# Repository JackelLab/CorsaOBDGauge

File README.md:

Bluetooth OBD Based Gauge For The Vauxhall/Opel Corsa

Anyone who owns an early Corsa knows you can't show the battery percentage on the dash
without having the car plugged in to a charger. The only other way is using an app on
your phone connected to and Bluetooth OBD adaptor (or WiFi adaptor if you have an iphone).

The problem with using an app (like 'Car Scanner' is that you need to connect to the
adaptor and then the car every time you want to see the data.

I decided (too long ago) that I wanted to make a display which showed the battery
percentage so it was always visible. My biggest stumbling block to this was understanding
what requests to send to the car and how to decode this data. After sometime, I found
some details on another github page 'EVNotify' which mentioned what data needed to be
sent and what the responses would be:
https://github.com/EVNotify/EVNotify/issues/205

With this information, I was finally able to get access to the data from the car.

I built a PCB with an ESP32-WROVER-IE as the main processor as it has Bluetooth built in,
a 0.96" LCD from ebay with 160 x 80 pixel 65k colours.

The features I've added so far are:

SOC        - Battery state of charge. I've used the non calibrated version, I don't know
what the differences are.

SOH        - Battery state of health. This only shows after the unit has setup and
checked communications with the OBD adaptor and car.

SOC Delta  - State of charge change. This shows to SOC change since the unit was powered
up, ideal for tracking how much battery has been used for a journey or how much battery
has been added while charging.

Temperature - Battery temperature.

Speed       - Shows the speed in 100th of MPH which can be re-calibrated if measured
against a GPS speedo.

Voltage     - OBD 12V battery voltage. Measured at the OBD adaptor.

Est. Range  - Estimated range based on speed and battery percentage used over the last
minute and 5 minutes.

There is a reed switch to change the display modes, the gauge will remember the last mode
and restore it at power up.

The ELM327 OBD.

When selecting a Bluetooth OBD adaptor, you will need to find one with the PIC18F25K80
chip. May of the adaptors for sale will say they are PIC versions, but often, they are
emulated versions and for whatever reason, the ESP32 can't communicate correctly with
them and just receives echoed data back.

So, ELM Electronics created the ELM327 chip for communicating with the OBD port on
vehicles, but with their version 1.5 software, chips where sent out without the code
protection on and so this code has been copied by may of the Chinese manufactures making
the currently available adaptors. If the adaptor you are looking to buy has any mention of
V2.1, then it is more likely a chip pretending to be a PIC.

The only way to really confirm that the adaptor has a PIC chip in it is to pop it open and
check.

My code requires you to put in the MAC address of the OBD adaptor, here are 2 ways you can
find the MAC address. Use an ESP32 to scan for Bluetooth devices and report the addresses
( https://github.com/esp32beans/ESP32-BT-exp ) or pair with a windows machine and get the
MAC address from the device details.

The alternative way, would be to use WiFi versions of the adaptor. At the moment, I've not
done any development on this method but may look into it in the future.

Another thing to note, not all adaptors have the correct resistors to do voltage
measurement and some that do, may not have been calibrated. Check the voltage with a volt
meter and compare that with the adaptor. Calibration would need to be done through a
computer with a terminal program.

Currently, the enclosure you can download is just a simple cover to hide and protect the
board, a friend is currently trying to map the instrument cluster to make a neater, almost
factory style, cover for the board which will sit to the right of the current instrument
cluster.

WIP..

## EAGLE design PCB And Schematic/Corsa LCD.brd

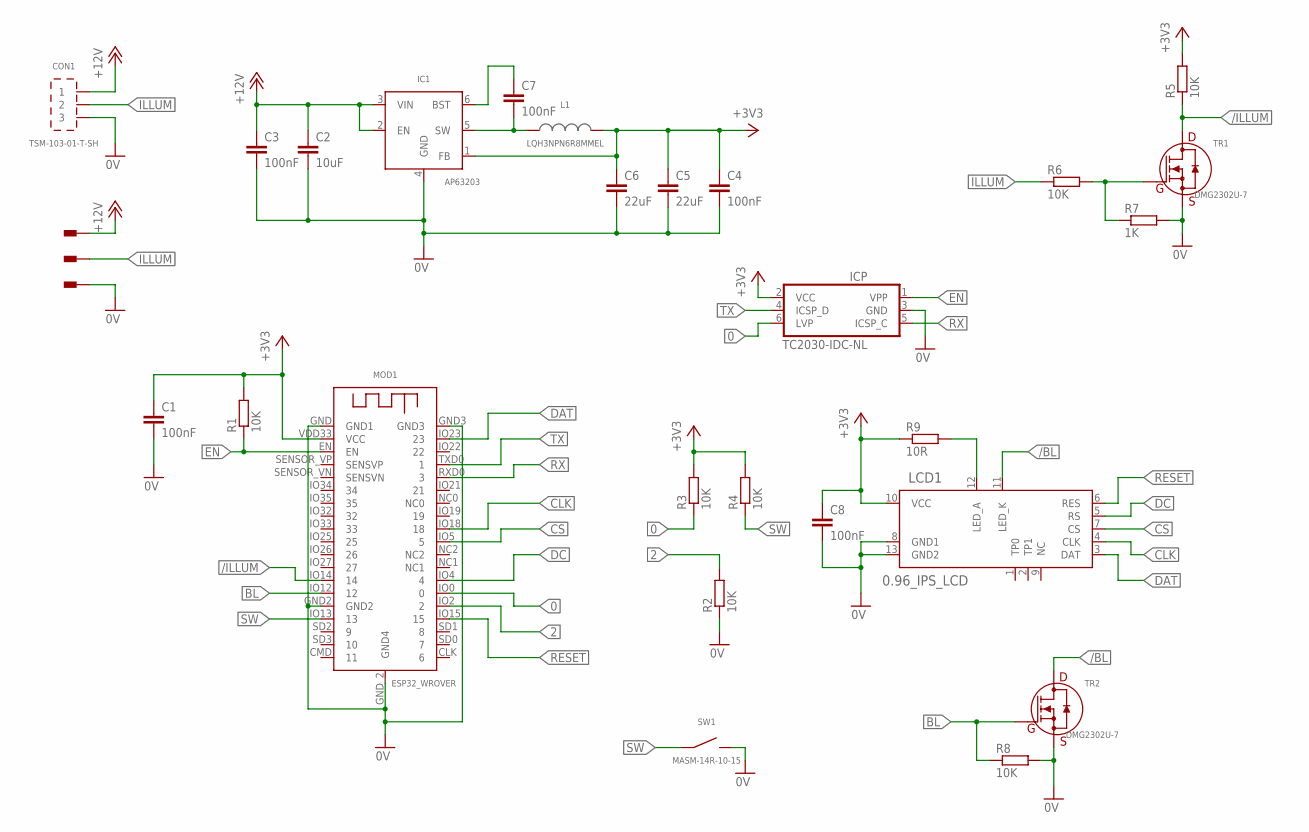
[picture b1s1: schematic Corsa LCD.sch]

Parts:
C1, C3, C4, C7, C8: 100nF; C0603
C2: 10uF; C0603
C5, C6: 22uF; C0603
CON1: TSM-103-01-T-SH
IC1: AP63203; TSOT26
ICP: TC2030-IDC-NL
L1: LQH3NPN6R8MMEL; LQH3NPN
LCD1: 0.96_IPS_LCD
MOD1: ESP32_WROVER; ESP32_WROOVER
PIN1, PIN2, PIN3: SOLDERPAD
R1, R2, R3, R4, R5, R6, R8: 10K; R0603
R7: 1K; R0603
R9: 10R; R0603
SW1: MASM-14R-10-15; MASM-14
TR1, TR2: DMG2302U-7; SOT23

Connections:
0: ICP.6 (LVP), MOD1.IO0 (0), R3.1
0V: C1.2, C2.2, C3.2, C4.2, C5.2, C6.2, C8.2, CON1.3, IC1.4 (GND), ICP.3 (GND), LCD1.8 (GND1), LCD1.13 (GND2), MOD1.GND (GND1), MOD1.GND2, MOD1.GND3, MOD1.GND_2 (GND4), PIN3.1, R2.1, R7.2, R8.2, SW1.2, TR1.2 (S), TR2.2 (S)
2: MOD1.IO2 (2), R2.2
+3V3: C1.1, C4.1, C5.1, C6.1, C8.1, IC1.1 (FB), ICP.2 (VCC), L1.2, LCD1.10 (VCC), MOD1.VDD33 (VCC), R1.2, R3.2, R4.2, R5.2, R9.1
+12V: C2.1, C3.1, CON1.1, IC1.2 (EN), IC1.3 (VIN), PIN1.1
/BL: LCD1.11 (LED_K), TR2.3 (D)
/ILLUM: MOD1.IO14 (14), R5.1, TR1.3 (D)
BL: MOD1.IO12 (12), R8.1, TR2.1 (G)
CLK: LCD1.4 (CLK), MOD1.IO18 (18)
CS: LCD1.7 (CS), MOD1.IO5 (5)
DAT: LCD1.3 (DAT), MOD1.IO23 (23)
DC: LCD1.5 (RS), MOD1.IO4 (4)
EN: ICP.1 (VPP), MOD1.EN, R1.1
ILLUM: CON1.2, PIN2.1, R6.1
unnamed: LCD1.12 (LED_A), R9.2
unnamed: R6.2, R7.1, TR1.1 (G)
unnamed: C7.1, IC1.6 (BST)
unnamed: C7.2, IC1.5 (SW), L1.1
RESET: LCD1.6 (RES), MOD1.IO15 (15)
RX: ICP.5 (ICSP_C), MOD1.RXD0 (3)
SW: MOD1.IO13 (13), R4.1, SW1.1
TX: ICP.4 (ICSP_D), MOD1.TXD0 (1)

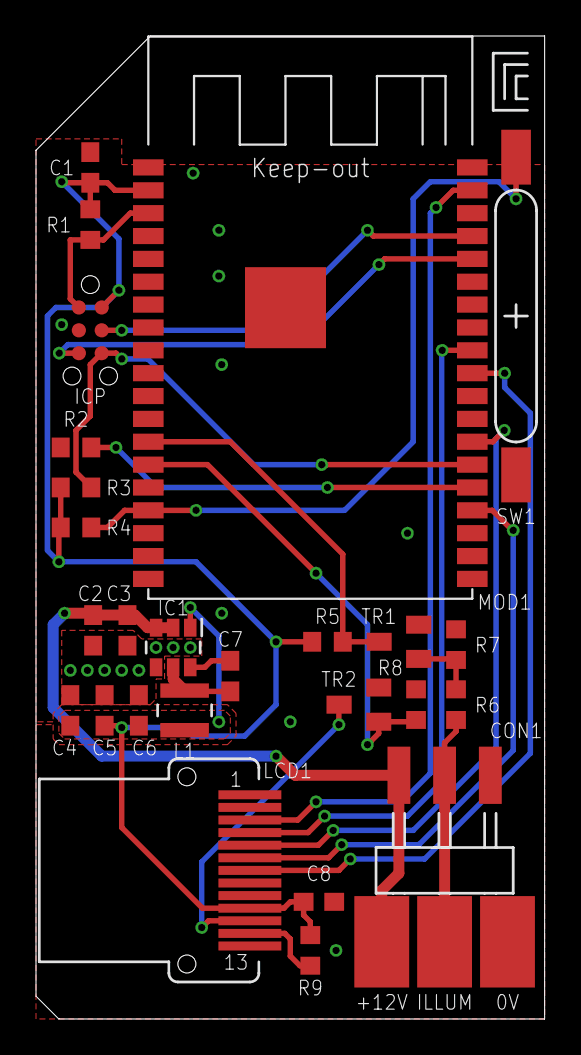
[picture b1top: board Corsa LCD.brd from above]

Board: 2 copper layers, 28.3 x 54.6 mm, 29 parts (0 on the bottom side), 22 nets.

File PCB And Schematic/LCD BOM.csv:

Ref,Desc,Package,Qty,PN,Manu,Notes
"C1,C3-C4,C7-C8",100nF Capacitor 50V,0603,5,Any,Any,
C2,10uF Capacitor 25V X5R,0603,1,Any,Any,
C5-C6,22uF Capacitor 6.3V X5R,0603,2,Any,Any,
CON1,3 Way RA Pin Header,,1,TSM-102-01-T-SH,Samtec,Can solder wires to pads instead
CON2,Tag 6 Pin Programming Header,,NF,,,
IC1,3.3V FixedBuck Regulator,TSOT-26-6,1,AP63203WU-7,Diodes Inc,
L1,6.8uH Inductor,,1,LQH3NPN6R8MMEL,MURATA,Or equivelent with same footprint
LCD1,"ST7735 0.96"" 160x80 Pixel LCD (Solder Type)",,1,LH096NT-IG11G,Limito,Soldered direct to the board
MOD1,ESP32-Wrover,,1,ESP32-WROVER-IE 8MB,Expressif,
"R1-R6,R8",10K 1% Resistor,0603,7,Any,Any,
R7,1K 1% Resistor,0603,1,Any,Any,
R9,10R 1% Resistor,0603,1,Any,Any,
Rx,0R Link,0201,1,Any,Any,Used to replace the link on the ESP32 Module
SW1,Reed Switch,,1,MASM-14R-10-15,Littelfuse,
TR1-TR2,N-Channel Power MOSFET,SOT23,2,DMG2302U-7,Dides Inc,

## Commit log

2024-03-07 Update LICENSE
